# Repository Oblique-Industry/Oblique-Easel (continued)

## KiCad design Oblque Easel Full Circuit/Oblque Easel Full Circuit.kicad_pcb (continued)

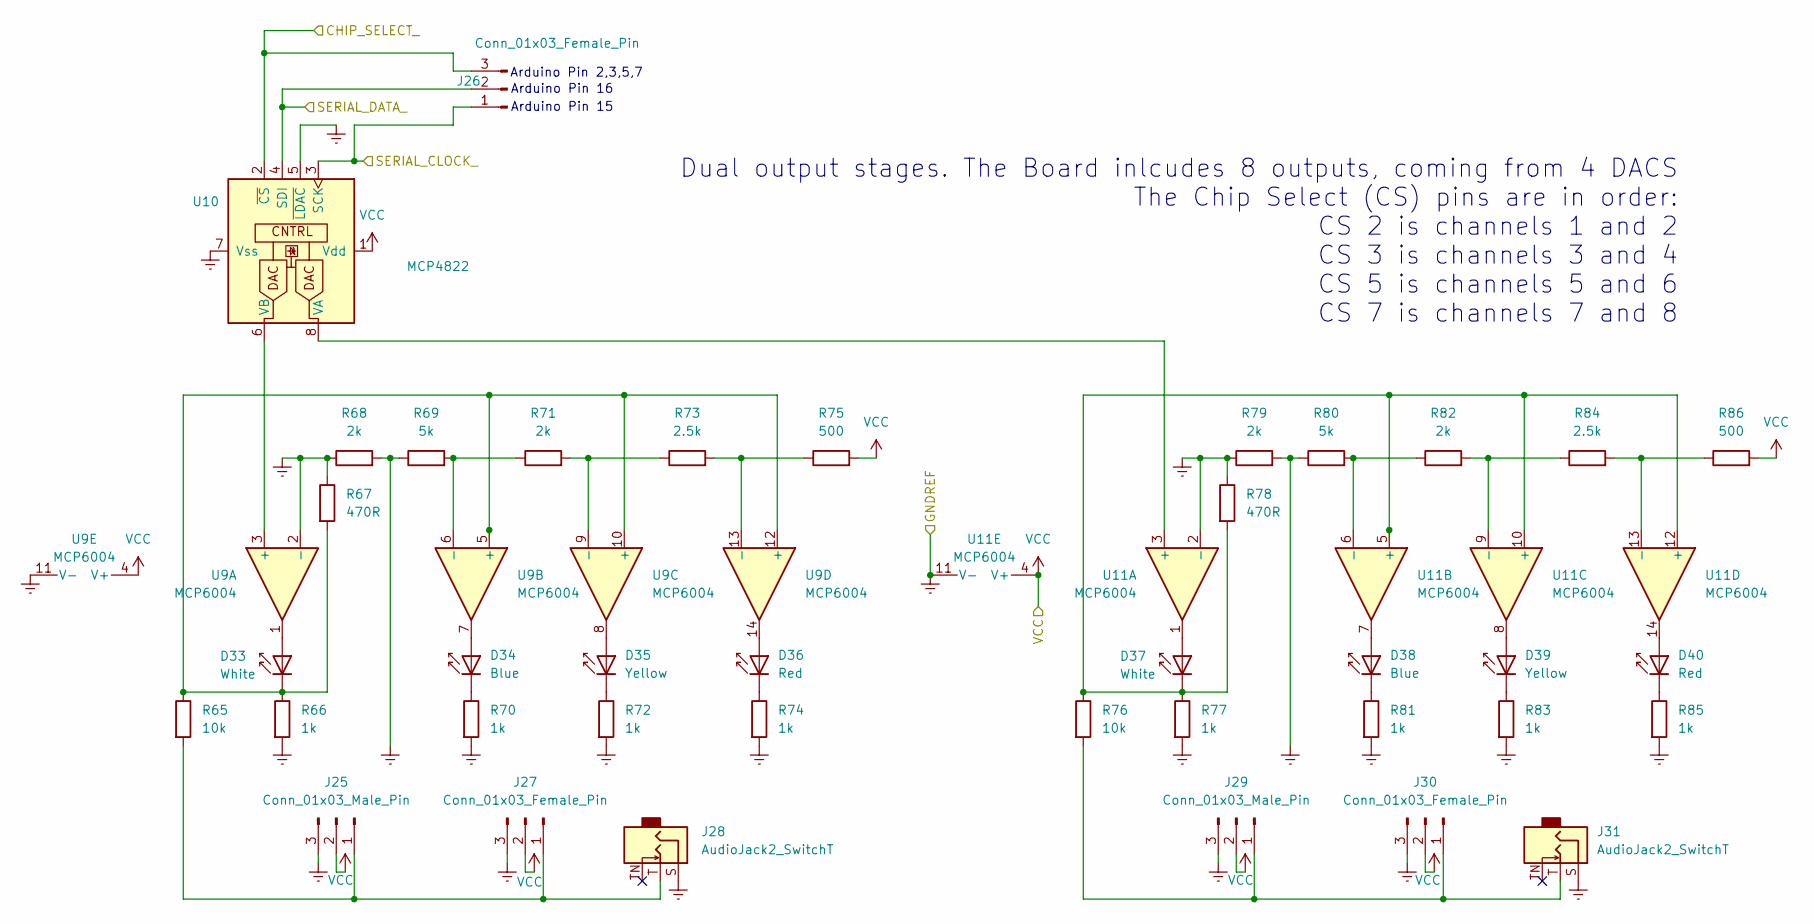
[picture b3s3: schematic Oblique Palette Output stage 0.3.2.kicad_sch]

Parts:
D33, D37: White; LED_SideEmitter_Rectangular_W4.5mm_H1.6mm
D34, D38: Blue; LED_SideEmitter_Rectangular_W4.5mm_H1.6mm
D35, D39: Yellow; LED_SideEmitter_Rectangular_W4.5mm_H1.6mm
D36, D40: Red; LED_SideEmitter_Rectangular_W4.5mm_H1.6mm
J25, J29: Conn_01x03_Male_Pin; PinHeader_1x03_P2.54mm_Vertical
J26, J27, J30: Conn_01x03_Female_Pin; PinSocket_1x03_P2.54mm_Vertical
J28, J31: AudioJack2_SwitchT; Jack_3.5mm_QingPu_WQP-PJ398SM_Vertical_CircularHoles
R65, R76: 10k; R_Axial_DIN0207_L6.3mm_D2.5mm_P2.54mm_Vertical
R66, R70, R72, R74, R77, R81, R83, R85: 1k; R_Axial_DIN0207_L6.3mm_D2.5mm_P2.54mm_Vertical
R67, R78: 470R; R_Axial_DIN0207_L6.3mm_D2.5mm_P2.54mm_Vertical
R68, R71, R79, R82: 2k; R_Axial_DIN0207_L6.3mm_D2.5mm_P2.54mm_Vertical
R69, R80: 5k; R_Axial_DIN0207_L6.3mm_D2.5mm_P2.54mm_Vertical
R73, R84: 2.5k; R_Axial_DIN0207_L6.3mm_D2.5mm_P2.54mm_Vertical
R75, R86: 500; R_Axial_DIN0207_L6.3mm_D2.5mm_P2.54mm_Vertical
U9, U11: MCP6004; DIP-14_W7.62mm_Socket_LongPads
U10: MCP4822; DIP-8_W7.62mm_Socket_LongPads

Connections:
/Output12/CHIP_SELECT_: J26.3, U10.2 (~CS); also elsewhere on the board
/Output12/SERIAL_CLOCK_: J26.1, U10.3 (SCK); also elsewhere on the board
/Output12/SERIAL_DATA_: J26.2, U10.4 (SDI); also elsewhere on the board
GNDREF: J25.3, J27.3, J28.S, J29.3, J30.3, J31.S, R66.2, R67.1, R68.1, R68.2, R69.1, R70.2, R72.2, R74.2, R77.2, R78.1, R79.1, R79.2, R80.1, R81.2, R83.2, R85.2, U9.2 (-), U9.11 (V-), U10.5 (~LDAC), U10.7 (Vss), U11.2 (-), U11.11 (V-); also elsewhere on the board
unnamed: D33.2 (A), U9.1
unnamed: D33.1 (K), R65.1, R66.1, R67.2, U9.5 (+), U9.10 (+), U9.12 (+)
unnamed: D34.2 (A), U9.7
unnamed: D34.1 (K), R70.1
unnamed: D35.2 (A), U9.8
unnamed: D35.1 (K), R72.1
unnamed: D36.2 (A), U9.14
unnamed: D36.1 (K), R74.1
unnamed: D37.2 (A), U11.1
unnamed: D37.1 (K), R76.1, R77.1, R78.2, U11.5 (+), U11.10 (+), U11.12 (+)
unnamed: D38.2 (A), U11.7
unnamed: D38.1 (K), R81.1
unnamed: D39.2 (A), U11.8
unnamed: D39.1 (K), R83.1
unnamed: D40.2 (A), U11.14
unnamed: D40.1 (K), R85.1
unnamed: J25.1, J27.1, J28.T, R65.2
unnamed: J29.1, J30.1, J31.T, R76.2
unnamed: R69.2, R71.1, U9.6 (-)
unnamed: R71.2, R73.1, U9.9 (-)
unnamed: R73.2, R75.1, U9.13 (-)
unnamed: U10.8 (VA), U11.3 (+)
unnamed: U9.3 (+), U10.6 (VB)
unnamed: R80.2, R82.1, U11.6 (-)
unnamed: R82.2, R84.1, U11.9 (-)
unnamed: R84.2, R86.1, U11.13 (-)
VCC: J25.2, J27.2, J29.2, J30.2, R75.2, R86.2, U9.4 (V+), U10.1 (Vdd), U11.4 (V+); also elsewhere on the board

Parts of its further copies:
D41, D45, D49, D53, D57, D61: White; LED_SideEmitter_Rectangular_W4.5mm_H1.6mm
D42, D46, D50, D54, D58, D62: Blue; LED_SideEmitter_Rectangular_W4.5mm_H1.6mm
D43, D47, D51, D55, D59, D63: Yellow; LED_SideEmitter_Rectangular_W4.5mm_H1.6mm
D44, D48, D52, D56, D60, D64: Red; LED_SideEmitter_Rectangular_W4.5mm_H1.6mm
J32, J36, J39, J43, J46, J50: Conn_01x03_Male_Pin; PinHeader_1x03_P2.54mm_Vertical
J33, J34, J37, J40, J41, J44, J47, J48, J51: Conn_01x03_Female_Pin; PinSocket_1x03_P2.54mm_Vertical
J35, J38, J42, J45, J49, J52: AudioJack2_SwitchT; Jack_3.5mm_QingPu_WQP-PJ398SM_Vertical_CircularHoles
R87, R98, R109, R120, R131, R142: 10k; R_Axial_DIN0207_L6.3mm_D2.5mm_P2.54mm_Vertical
R88, R92, R94, R96, R99, R103, R105, R107, R110, R114, R116, R118, R121, R125, R127, R129, R132, R136, R138, R140, R143, R147, R149, R151: 1k; R_Axial_DIN0207_L6.3mm_D2.5mm_P2.54mm_Vertical
R89, R100, R111, R122, R133, R144: 470R; R_Axial_DIN0207_L6.3mm_D2.5mm_P2.54mm_Vertical
R90, R93, R101, R104, R112, R115, R123, R126, R134, R137, R145, R148: 2k; R_Axial_DIN0207_L6.3mm_D2.5mm_P2.54mm_Vertical
R91, R102, R113, R124, R135, R146: 5k; R_Axial_DIN0207_L6.3mm_D2.5mm_P2.54mm_Vertical
R95, R106, R117, R128, R139, R150: 2.5k; R_Axial_DIN0207_L6.3mm_D2.5mm_P2.54mm_Vertical
R97, R108, R119, R130, R141, R152: 500; R_Axial_DIN0207_L6.3mm_D2.5mm_P2.54mm_Vertical
U13, U15, U16, U18, U19, U21: MCP6004; DIP-14_W7.62mm_Socket_LongPads
U14, U17, U20: MCP4822; DIP-8_W7.62mm_Socket_LongPads

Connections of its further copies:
/Output12/SERIAL_CLOCK_: J33.1, J40.1, J47.1, U14.3 (SCK), U17.3 (SCK), U20.3 (SCK); also elsewhere on the board
/Output12/SERIAL_DATA_: J33.2, J40.2, J47.2, U14.4 (SDI), U17.4 (SDI), U20.4 (SDI); also elsewhere on the board
/Output34/CHIP_SELECT_: J33.3, U14.2 (~CS); also elsewhere on the board
/Output56/CHIP_SELECT_: J40.3, U17.2 (~CS); also elsewhere on the board
/Output78/CHIP_SELECT_: J47.3, U20.2 (~CS); also elsewhere on the board
GNDREF: J32.3, J34.3, J35.S, J36.3, J37.3, J38.S, J39.3, J41.3, J42.S, J43.3, J44.3, J45.S, J46.3, J48.3, J49.S, J50.3, J51.3, J52.S, R88.2, R89.1, R90.1, R90.2, R91.1, R92.2, R94.2, R96.2, R99.2, R100.1, R101.1, R101.2, R102.1, R103.2, R105.2, R107.2, R110.2, R111.1, R112.1, R112.2, R113.1, R114.2, R116.2, R118.2, R121.2, R122.1, R123.1, R123.2, R124.1, R125.2, R127.2, R129.2, R132.2, R133.1, R134.1, R134.2, R135.1, R136.2, R138.2, R140.2, R143.2, R144.1, R145.1, R145.2, R146.1, R147.2, R149.2, R151.2, U13.2 (-), U13.11 (V-), U14.5 (~LDAC), U14.7 (Vss), U15.2 (-), U15.11 (V-), U16.2 (-), U16.11 (V-), U17.5 (~LDAC), U17.7 (Vss), U18.2 (-), U18.11 (V-), U19.2 (-), U19.11 (V-), U20.5 (~LDAC), U20.7 (Vss), U21.2 (-), U21.11 (V-); also elsewhere on the board
unnamed: D41.2 (A), U13.1
unnamed: D41.1 (K), R87.1, R88.1, R89.2, U13.5 (+), U13.10 (+), U13.12 (+)
unnamed: D42.2 (A), U13.7
unnamed: D42.1 (K), R92.1
unnamed: D43.2 (A), U13.8
unnamed: D43.1 (K), R94.1
unnamed: D44.2 (A), U13.14
unnamed: D44.1 (K), R96.1
unnamed: D45.2 (A), U15.1
unnamed: D45.1 (K), R98.1, R99.1, R100.2, U15.5 (+), U15.10 (+), U15.12 (+)
unnamed: D46.2 (A), U15.7
unnamed: D46.1 (K), R103.1
unnamed: D47.2 (A), U15.8
unnamed: D47.1 (K), R105.1
unnamed: D48.2 (A), U15.14
unnamed: D48.1 (K), R107.1
unnamed: D49.2 (A), U16.1
unnamed: D49.1 (K), R109.1, R110.1, R111.2, U16.5 (+), U16.10 (+), U16.12 (+)
unnamed: D50.2 (A), U16.7
unnamed: D50.1 (K), R114.1
unnamed: D51.2 (A), U16.8
unnamed: D51.1 (K), R116.1
unnamed: D52.2 (A), U16.14
unnamed: D52.1 (K), R118.1
unnamed: D53.2 (A), U18.1
unnamed: D53.1 (K), R120.1, R121.1, R122.2, U18.5 (+), U18.10 (+), U18.12 (+)
unnamed: D54.2 (A), U18.7
unnamed: D54.1 (K), R125.1
unnamed: D55.2 (A), U18.8
unnamed: D55.1 (K), R127.1
unnamed: D56.2 (A), U18.14
unnamed: D56.1 (K), R129.1
unnamed: D57.2 (A), U19.1
unnamed: D57.1 (K), R131.1, R132.1, R133.2, U19.5 (+), U19.10 (+), U19.12 (+)
unnamed: D58.2 (A), U19.7
unnamed: D58.1 (K), R136.1
unnamed: D59.2 (A), U19.8
unnamed: D59.1 (K), R138.1
unnamed: D60.2 (A), U19.14
unnamed: D60.1 (K), R140.1
unnamed: D61.2 (A), U21.1
unnamed: D61.1 (K), R142.1, R143.1, R144.2, U21.5 (+), U21.10 (+), U21.12 (+)
unnamed: D62.2 (A), U21.7
unnamed: D62.1 (K), R147.1
unnamed: D63.2 (A), U21.8
unnamed: D63.1 (K), R149.1
unnamed: D64.2 (A), U21.14
unnamed: D64.1 (K), R151.1
unnamed: J32.1, J34.1, J35.T, R87.2
unnamed: J36.1, J37.1, J38.T, R98.2
unnamed: J39.1, J41.1, J42.T, R109.2
unnamed: J43.1, J44.1, J45.T, R120.2
unnamed: J46.1, J48.1, J49.T, R131.2
unnamed: J50.1, J51.1, J52.T, R142.2
unnamed: U13.3 (+), U14.6 (VB)
unnamed: R91.2, R93.1, U13.6 (-)
unnamed: R93.2, R95.1, U13.9 (-)
unnamed: R95.2, R97.1, U13.13 (-)
unnamed: U14.8 (VA), U15.3 (+)
unnamed: R102.2, R104.1, U15.6 (-)
unnamed: R104.2, R106.1, U15.9 (-)
unnamed: R106.2, R108.1, U15.13 (-)
unnamed: U16.3 (+), U17.6 (VB)
unnamed: R113.2, R115.1, U16.6 (-)
unnamed: R115.2, R117.1, U16.9 (-)
unnamed: R117.2, R119.1, U16.13 (-)
unnamed: U17.8 (VA), U18.3 (+)
unnamed: R124.2, R126.1, U18.6 (-)
unnamed: R126.2, R128.1, U18.9 (-)
unnamed: R128.2, R130.1, U18.13 (-)
unnamed: U19.3 (+), U20.6 (VB)
unnamed: R135.2, R137.1, U19.6 (-)
unnamed: R137.2, R139.1, U19.9 (-)
unnamed: R139.2, R141.1, U19.13 (-)
unnamed: U20.8 (VA), U21.3 (+)
unnamed: R146.2, R148.1, U21.6 (-)
unnamed: R148.2, R150.1, U21.9 (-)
unnamed: R150.2, R152.1, U21.13 (-)
VCC: J32.2, J34.2, J36.2, J37.2, J39.2, J41.2, J43.2, J44.2, J46.2, J48.2, J50.2, J51.2, R97.2, R108.2, R119.2, R130.2, R141.2, R152.2, U13.4 (V+), U14.1 (Vdd), U15.4 (V+), U16.4 (V+), U17.1 (Vdd), U18.4 (V+), U19.4 (V+), U20.1 (Vdd), U21.4 (V+); also elsewhere on the board

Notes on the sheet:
Arduino Pin 2,3,5,7
Dual output stages. The Board inlcudes 8 outputs, coming from 4 DACS The Chip Select (CS) pins are in order: CS 2 is channels 1 and 2 CS 3 is channels 3 and 4 CS 5 is channels 5 and 6 CS 7 is channels 7 and 8
Arduino Pin 16
Arduino Pin 15

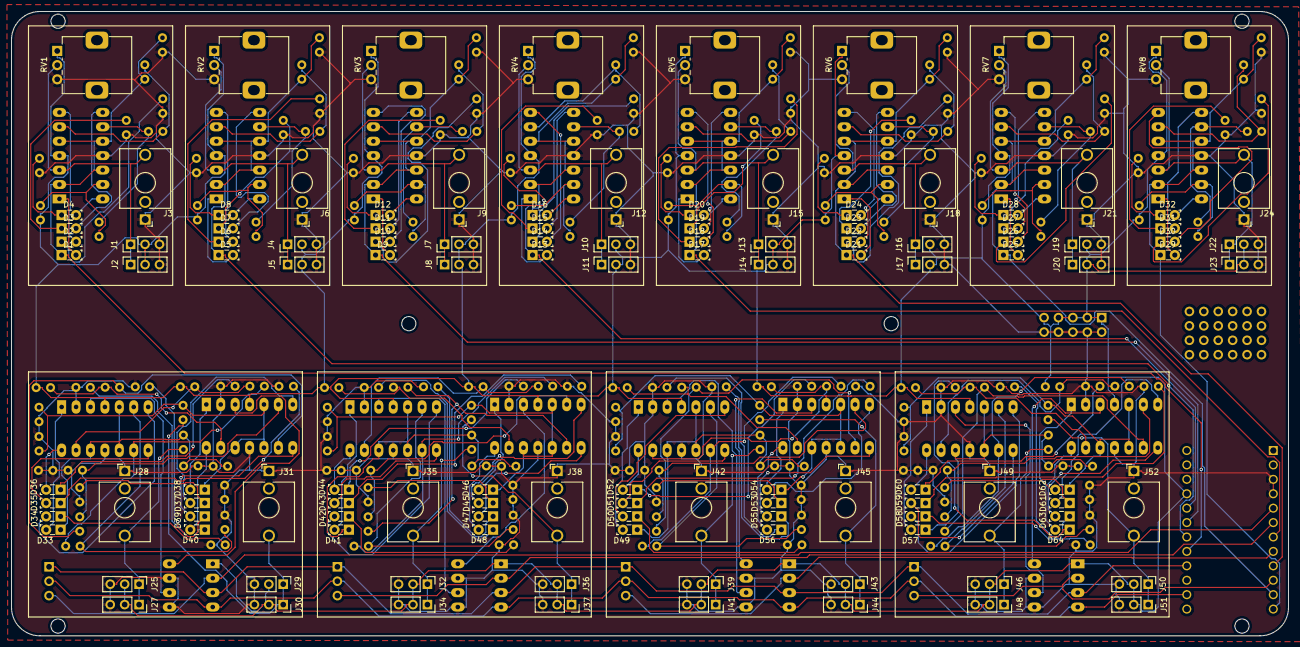
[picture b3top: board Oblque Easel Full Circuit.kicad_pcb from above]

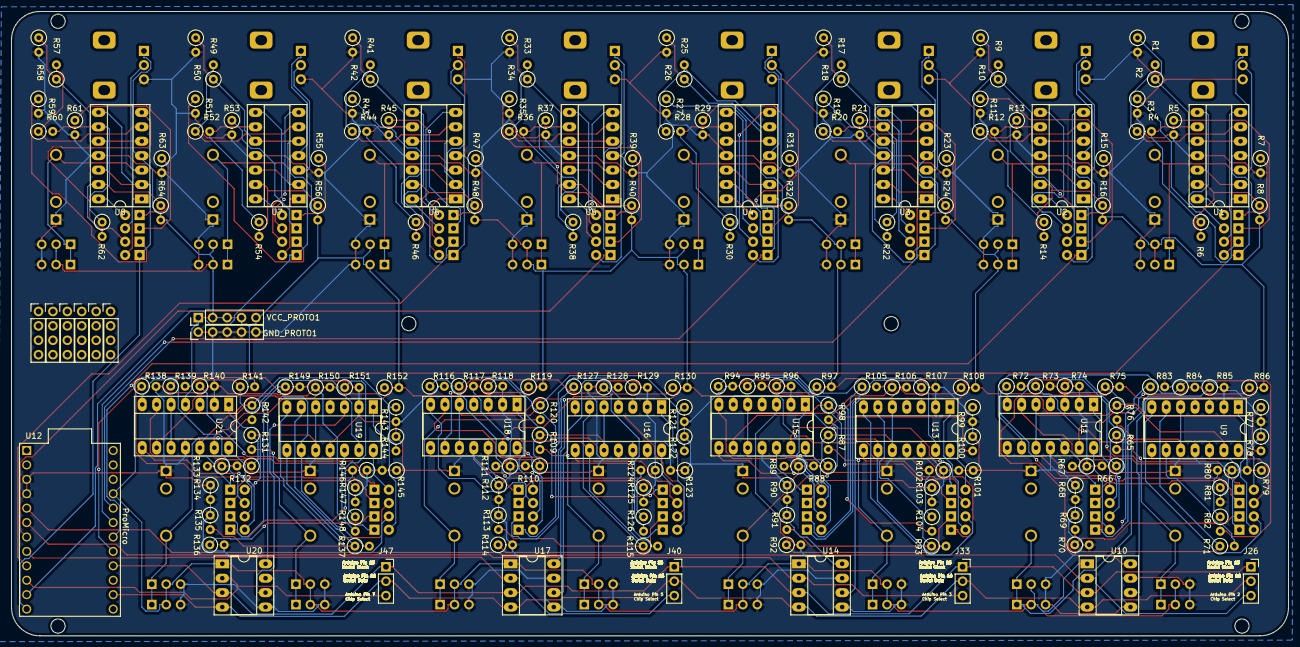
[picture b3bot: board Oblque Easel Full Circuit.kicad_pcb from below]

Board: 2 copper layers, 225.0 x 110.0 mm, 305 parts (185 on the bottom side), 208 nets.

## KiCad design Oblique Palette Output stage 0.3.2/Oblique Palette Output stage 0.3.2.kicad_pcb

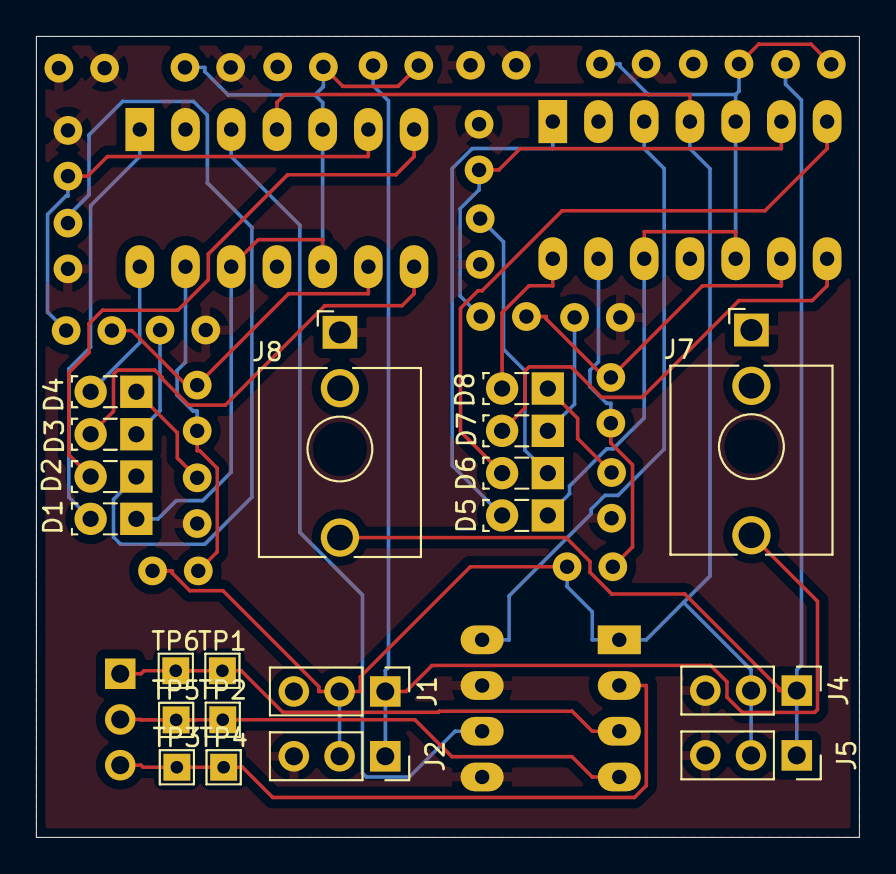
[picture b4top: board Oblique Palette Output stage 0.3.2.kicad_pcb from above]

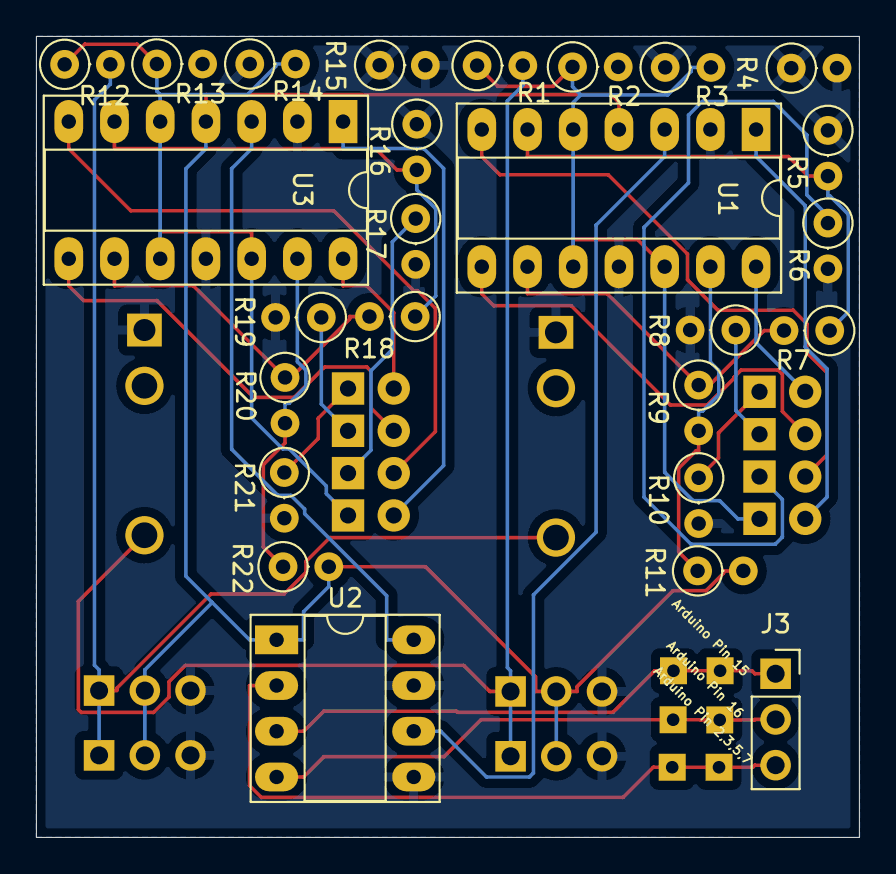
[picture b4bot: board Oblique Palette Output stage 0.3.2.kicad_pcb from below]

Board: 2 copper layers, 45.7 x 44.5 mm, 46 parts (26 on the bottom side), 31 nets.

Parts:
D1, D5: White; LED_SideEmitter_Rectangular_W4.5mm_H1.6mm
D2, D6: Blue; LED_SideEmitter_Rectangular_W4.5mm_H1.6mm
D3, D7: Yellow; LED_SideEmitter_Rectangular_W4.5mm_H1.6mm
D4, D8: Red; LED_SideEmitter_Rectangular_W4.5mm_H1.6mm
J1, J4: Conn_01x03_Male_Pin; PinHeader_1x03_P2.54mm_Vertical
J2, J3, J5: Conn_01x03_Female_Pin; PinSocket_1x03_P2.54mm_Vertical
J7, J8: AudioJack2_SwitchT; Jack_3.5mm_QingPu_WQP-PJ398SM_Vertical_CircularHoles
R1, R12: 10k; R_Axial_DIN0207_L6.3mm_D2.5mm_P2.54mm_Vertical
R2, R6, R8, R10, R13, R17, R19, R21: 1k; R_Axial_DIN0207_L6.3mm_D2.5mm_P2.54mm_Vertical
R3, R14: 470R; R_Axial_DIN0207_L6.3mm_D2.5mm_P2.54mm_Vertical
R4, R7, R15, R18: 2k; R_Axial_DIN0207_L6.3mm_D2.5mm_P2.54mm_Vertical
R5, R16: 5k; R_Axial_DIN0207_L6.3mm_D2.5mm_P2.54mm_Vertical
R9, R20: 2.5k; R_Axial_DIN0207_L6.3mm_D2.5mm_P2.54mm_Vertical
R11, R22: 500; R_Axial_DIN0207_L6.3mm_D2.5mm_P2.54mm_Vertical
TP1, TP2, TP3, TP4, TP5, TP6: TestPoint; TestPoint_THTPad_1.5x1.5mm_Drill0.7mm
U1, U3: MCP6004; DIP-14_W7.62mm_Socket_LongPads
U2: MCP4822; DIP-8_W7.62mm_Socket_LongPads

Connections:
GNDREF: J1.3, J2.3, J4.3, J5.3, J7.S, J8.S, R2.2, R3.1, R4.1, R4.2, R5.1, R6.2, R8.2, R10.2, R13.2, R14.1, R15.1, R15.2, R16.1, R17.2, R19.2, R21.2, U1.2 (-), U1.11 (V-), U2.5 (~LDAC), U2.7 (Vss), U3.2 (-), U3.11 (V-)
unnamed: D1.2 (A), U1.1
unnamed: D1.1 (K), R1.1, R2.1, R3.2, U1.5 (+), U1.10 (+), U1.12 (+)
unnamed: D2.2 (A), U1.7
unnamed: D2.1 (K), R6.1
unnamed: D3.2 (A), U1.8
unnamed: D3.1 (K), R8.1
unnamed: D4.2 (A), U1.14
unnamed: D4.1 (K), R10.1
unnamed: D5.2 (A), U3.1
unnamed: D5.1 (K), R12.1, R13.1, R14.2, U3.5 (+), U3.10 (+), U3.12 (+)
unnamed: D6.2 (A), U3.7
unnamed: D6.1 (K), R17.1
unnamed: D7.2 (A), U3.8
unnamed: D7.1 (K), R19.1
unnamed: D8.2 (A), U3.14
unnamed: D8.1 (K), R21.1
unnamed: J1.1, J2.1, J7.T, R1.2
unnamed: J3.1, TP1.1, TP6.1, U2.3 (SCK)
unnamed: J3.2, TP2.1, TP5.1, U2.4 (SDI)
unnamed: J3.3, TP3.1, TP4.1, U2.2 (~CS)
unnamed: J4.1, J5.1, J8.T, R12.2
unnamed: U1.3 (+), U2.6 (VB)
unnamed: R5.2, R7.1, U1.6 (-)
unnamed: R7.2, R9.1, U1.9 (-)
unnamed: R9.2, R11.1, U1.13 (-)
unnamed: U2.8 (VA), U3.3 (+)
unnamed: R16.2, R18.1, U3.6 (-)
unnamed: R18.2, R20.1, U3.9 (-)
unnamed: R20.2, R22.1, U3.13 (-)
VCC: J1.2, J2.2, J4.2, J5.2, R11.2, R22.2, U1.4 (V+), U2.1 (Vdd), U3.4 (V+)

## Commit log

2024-03-26 Update README.md (#1)
2024-03-26 Development (#2)
    * Update README.md
    * Update README.md
2024-03-26 First fully functioning firmware version
    Firmware to be installed on the Arduino Pro Micro that is the communication heart of the Palette
2024-03-26 Palette Firmware (#3)
    * Update README.md
    * Update README.md
    * First fully functioning firmware version
    Firmware to be installed on the Arduino Pro Micro that is the communication heart of the Palette
2024-03-26 Circuit diagrams for Input and Output stages
2024-03-26 Circuit diagrams for input and output stages (#4)
    * Update README.md
    * Update README.md
    * First fully functioning firmware version
    Firmware to be installed on the Arduino Pro Micro that is the communication heart of the Palette
    * Circuit diagrams for Input and Output stages
2024-03-29 plugdata objects initial commit
2024-03-29 Development (#5)
    * Update README.md
    * Update README.md
    * First fully functioning firmware version
    Firmware to be installed on the Arduino Pro Micro that is the communication heart of the Palette
    * Circuit diagrams for Input and Output stages
    * plugdata objects initial commit
2024-04-05 Board technical drawing
2024-06-04 Logo added to board.
    Added logo and logotype to the board.
2024-06-05 Re-added Oblique logo to the front
2024-06-05 Fixed name, re-re-readded logo to PCB
2024-06-05 Logo silkscreen design finally verified.
2024-07-16 Fixed path bugs in Palette Input and Output
    Made sure library object path names were explicit.
2024-11-09 Building a buffer before sending data to the Palette
    Formatting output to be:
    # of channels[8],ch0*,ch1*,...\n
    e.g.
    8,512,1024,2048,3452,2643,1563,0,2367,2967,[that's all 8 channels, Then 99 more lists]\n
2024-11-15 Built a new communication buffer out of triplets of bytes that represent two 12-bit values.
    Divided pairs of values across two bytes
    Made a new output tile that does the division
    Made a new panel to hold tiles, though we're trying just one for now.
2025-02-21 Easel and Palette are now communicating!
    Easel:
    All communication is happening at one sample per cycle, about 100Hz.
    Palette:
    Analog in: Working!
    Analog out: not working. Communication with multiplexer isn't functioning. Wrong pins? Typo? Just hangs the board.
    Servo out: Working!
2025-02-21 DAC mux code is commented out to test servo code, which is working great.
2025-02-26 Putting in code to switch between DAC i2c busses
2025-02-27 Uploading KiCAD Versions
2025-02-28 Both i2c busses are now working for DACs.
    Remaining problem: actually writing to the DACs (or perhaps reading the values from Serial) causes the sample rate to drop from 1kHz to 1Hz. I'm pretty certain the 1Hz thing is a timeout, which means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
2025-02-28 All functions are now proven!
    ADC -> Easel is good
    DAC -> Palette is good
    DAC on both i2c busses is good
    DAC -> Servos is good!
    Weird:
    Servo is not rotating fully. This is, I think, in the firmware.
2025-02-28 Tidied up. All functions are working!
    Sample rate is only about 11Hz. Time to start bundling samples together.
2025-02-28 Flipped the servo direction.
2025-03-03 Fixed CD4051 Issues
2025-03-03 Minor edits before sending to JLCPCB
2025-03-03 Corrected ADC resolution. Continued clarifying the Easel patch.
2025-03-05 Test code to increase analog read speed.
2025-03-05 Cleaning up old versions into "obsolete" directories.
2025-03-06 PCB 0.5.2
2025-03-07 Update README.md
    Took out the "(test)" cuz it's not anymore.
2025-03-07 Working files of Version 0.5.2, organized folders. Added change log
2025-03-11 Reupload files to initialize GitHub Desktop
2025-03-11 RePush trying to establish GitHub Desktop
2025-03-15 PCB corrections for 0.5.3
    • Main output LED is now between op amp and feedback loop, so it will brighten at the first whiff of voltage.
    • Errant wire between VBus and input potentiometer will allow us to have signals other than 5V
    • Servos are now powered by V_SERVO as well as VBus.
    TO DO: Differentiate A0 and A1 DACs
2025-03-15 Archived old versions of the PCB.
2025-04-02 New design for the indicator and in/output op amp circuit
    This version has only 3 LEDs. The fourth LED was either too dim to be useful at lower voltages, or it was reducing output voltages above 3.3V.
2025-04-02 Pin corrections
2025-04-02 Corrections and refinements
2025-04-02 Corrected op amp circuits on INPUT
    Reduced from 4 LED indicators to 3, plus output.
    WHITE now glows increasing brightness from >0V up to 5V
    YELLOW turns on at 2.7V (a logical HIGH)
    RED turns on at 3.6V (the danger level for 3V circuits)
    The remaining op amp is now purely an output, now with a 1k resistor to reduce whoopsies while in use.
2025-04-02 Update OUTPUT channels with 3 LEDs and appropriate resistors
    Output channels how have RED (>3.6V), YELLOW (<2.7V) and WHITE (<0, increasing in brightness up to 5V) indicator LEDs.
    Output op amp now has a 1k resistor to prevent in-use whoopsies.
2025-04-02 Deleted redundant resistor
    Realized that the input between the op amp and the µC pin didn't need a current-limiting resistor because we know exactly what's going to be there.
2025-04-04 More input and output channel corrections
    Reduced the white LED inputs to have a range of 0V:3.3V to get a greater range of brightness across the range of values
    Powered the input op amps from 3v3 so we can't blow up. Changed the comparison voltage for the LEDs to 0V:3.3V instead of up to 5 so brightnesses are consistent between input and output channels.
2025-04-14 Front panel channel labels
2025-04-14 Stray line removal before autorouting
2025-04-14 Routed, all errors cleared (though there are still some silkscreen uglinesses)
2025-04-16 Re-routed with many errors fixed
    Found some unplaced resistors necessary for bringing output control voltages down to LED levels.
    Eliminated artifacts of previous drafts.
2025-04-16 Looks good to go.
    Just have to figure out how to export it for JLCPCB now.
2025-04-17 Little aesthetic adjustments
    Everything is done except designating which DAC channels are the A0 and which are the A1 variants.
2025-04-30 Fixing input channels
    Issues:
    1. Some (all?) input channels are not connected to the multiplexer. This seems to be an issue with my hierarchical labels?
    2. Input op amps do not seem to have inputs for the yellow and red LEDs. Again, they seem to be disconnected.
    Checked: levels coming out of the potentiometers are correct.
2025-06-04 All traces(?) now connected on PCB.
    This is looking good to me. Vcc and VServo are merged for simplicity. Not the best solution. I think maybe a breakable trace or a single jumper might be the way to do this.
2025-06-09 I've cleaned up all sorts of misplaced resistors. Manually routing input channel 1 to replicate across inputs.
2025-06-10 Input channels look to be all connected and logical now!
    All inputs have their designated resistors. Channels are connected to 3v3 and GND.
    Gonna beef up the power caps and turn them into SMDs.
    Also gonna do up the output channels.
2025-06-12 All traces connected. Replaced caps with 1mF SMD ones to add muffling power for and to the servos.
2025-06-15 Changed Directory Name to Oblique Pallette 0.5.x PCB Files and Copied 0.5.1 and created New 0.5.4 Project .
2025-06-18 Ugh. Looks like the connections to VCC and GND of the power caps got deleted in the last second. Fixed now, will see if I need to bridge on 0.5.4
2025-06-21 Corrected missing traces but good.
2025-07-03 Making traces beautiful.
2025-07-15 We get errors, but serial communication is up again!
    The good:
    1: All 8 ADC input channels s are working fine, if at a low sample rate. I realize that I haven't checked them against actual CV and I should
    2: Output channels 1-4 on i2c bus 0 are working fine.
    The bad:
    1: Output channels 5-8 aren't working. They should be on i2c bus 1, but I'm not confident they are. I can't find a ton of documentation on using i2c bus 1. My best, very hesitatnt, guess is that I'm 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
    2: Running a servo on a channel makes it extremely likely to burn out that channel's DAC chip! That means that, at LEAST the chip needs some sort of power connection, but it also emphasizes
2025-08-05 Looks like I just about finished up, only to realize that KiCAD re-designated all components.
    I think the PCB is all correct now, but it no longer matches the schematic. Committing now so I can roll back and redo with more incremental commits.
2025-08-05 Tidying up just so I can roll back changes to avoid the component re-designation catastrophe.
2025-08-06 Fixed that weird component re-designation problem. Everything looks ok now.
2025-08-16 Penultimate prep for JLCPCB manufacture. Have to place front side still.
2025-08-25 Might be ready for manufacture. Weird warning that says that the power caps are specified with a through-hole footprint, which they aren't.
2025-08-25 Added ident to sheet.
2025-08-25 Power capacitors now have the correct footprint. Only remaining errors are the unconnected debug pins from the Raspberry Pi Pico dev board, which, if the user wants to use them for some reason, shoul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
2025-08-27 Ready to go, but for some blank part numbers in the BOM to work out with the manufacturer.
2025-08-27 Whoops, last bits of saves weren't saved.
2025-09-05 File cleanup
2025-09-05 More file cleaup.
2025-09-26 Prep for manufacturing 0.5.5
2025-09-28 DAC ICs had ambiguous LCSC part numbers.
    U15 U17 U23 U25 are now LCSC part# C61423
2025-10-03 Associated Input and Output tiles relatively rather than absolutely, which got them lost in the sauce.
2025-10-19 Fixed the lack of outgoing data to the Palette
    It looks like I'd stopped feeding the output to [pd formatPacket], probably as part of an earlier bug hunt.
    Currently, you have to click [open 3] to start communication. The switch on the panel is disconnected, as it tries to turn itself on, leading to a stack overflow due to infinite loop.
2025-10-20 Hunting for two bugs: serial buffer overrun (pretty sure that's what's going on) and replacing legit ADC values with 0s.
2025-10-20 Firmware now communicates fully, though the sample rate randomly drops from 85Hz down to exactly 0.25Hz.
2025-10-20 Just unifying the way I'm using testBlink() to diagnose this weird drop to 0.25Hz.
2025-10-20 Fixed testBlink() so now it actually changes the state of the LED instead of just doing the opposite of being LOW every cycle.
2025-11-03 Hunting for bugs between Linux and Mac
    Palette works fine on Mac, though with a 40Hz sample rate.
    Palette works in Linux with a 340Hz sample rate but suddenly stops after a random number of seconds. It does *not* go down to a sample rate of 0.25 as it was doing before. The microcontroller just co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
2026-01-01 Breaking off 0.6.0 to try to work out comms issues
    First, separating serial comms from ADC and DAC processing into separate processors.
2026-01-01 Made Architeuthis Flux's recommended changes:
    Added "while (Serial.available() == 0" so it doesn't try to read before there's something to read
    Took out multithreading to keep the problem simple
    set Serial.timeout(500)
2026-01-02 Working in MacOS! Dual cores working, both in and output.
